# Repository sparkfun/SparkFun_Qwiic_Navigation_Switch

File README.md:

SparkFun Qwiic Navigational Switch
========================================

[](

[*SparkFun Qwiic Navigational Switch (PRT-27576)*](

<Basic description of the part.>

Repository Contents
-------------------

* **.github/workflows** - YAML files used for GitHub Actions and GitHub Pages/mkdocs
* **/Firmware** - Example code
* **/Hardware** - KiCad design files (.kicad_pcb, .kicad_sch, .kicad_pro)
* **/docs** - Online documentation files
  * **/assets** - Folder containing all the file assets used for product documentation
    * **/3d_model** - Exported 3D models from KiCad
    * **/board_files** - Copy of design files used for product documentation
    * **/component_documentation** - Datasheets and manuals for hardware components
    * **/img** - Images for product documentation
  * **/github** - Files stating how to contribute and filing issues used for product documentation
  * **/javascript** - Folder containing custom javascript used for product documentation
  * **/stylesheet** - Folder containing CSS files used for product documentation
* **/overrides** - Customization files used for product documentation
  * **/.icons** - Icons used for GitHub used for product documentation
  * **./partials** - Used for product documentation

Documentation
--------------
* **[Library](https://github.com/sparkfun/SparkFun_I2C_Expander_Arduino_Library)** - Arduino library for the Qwiic Navigational Switch.
* **[Hookup Guide](https://docs.sparkfun.com/SparkFun_Qwiic_Navigation_Switch/)** - Basic hookup guide for the Qwiic Navigational Switch.

Product Versions
----------------
* [PRT-27576](https://www.sparkfun.com/products/27576) - v1.1

Version History
---------------
* v1.1 - Initial Release

License Information
-------------------

This product is _**open source**_!

Please review the LICENSE.md file for license information.

If you have any questions or concerns on licensing, please contact technical support on our [SparkFun forums](https://forum.sparkfun.com/viewforum.php?f=152).

Distributed as-is; no warranty is given.

- Your friends at SparkFun.

_<COLLABORATION CREDIT>_

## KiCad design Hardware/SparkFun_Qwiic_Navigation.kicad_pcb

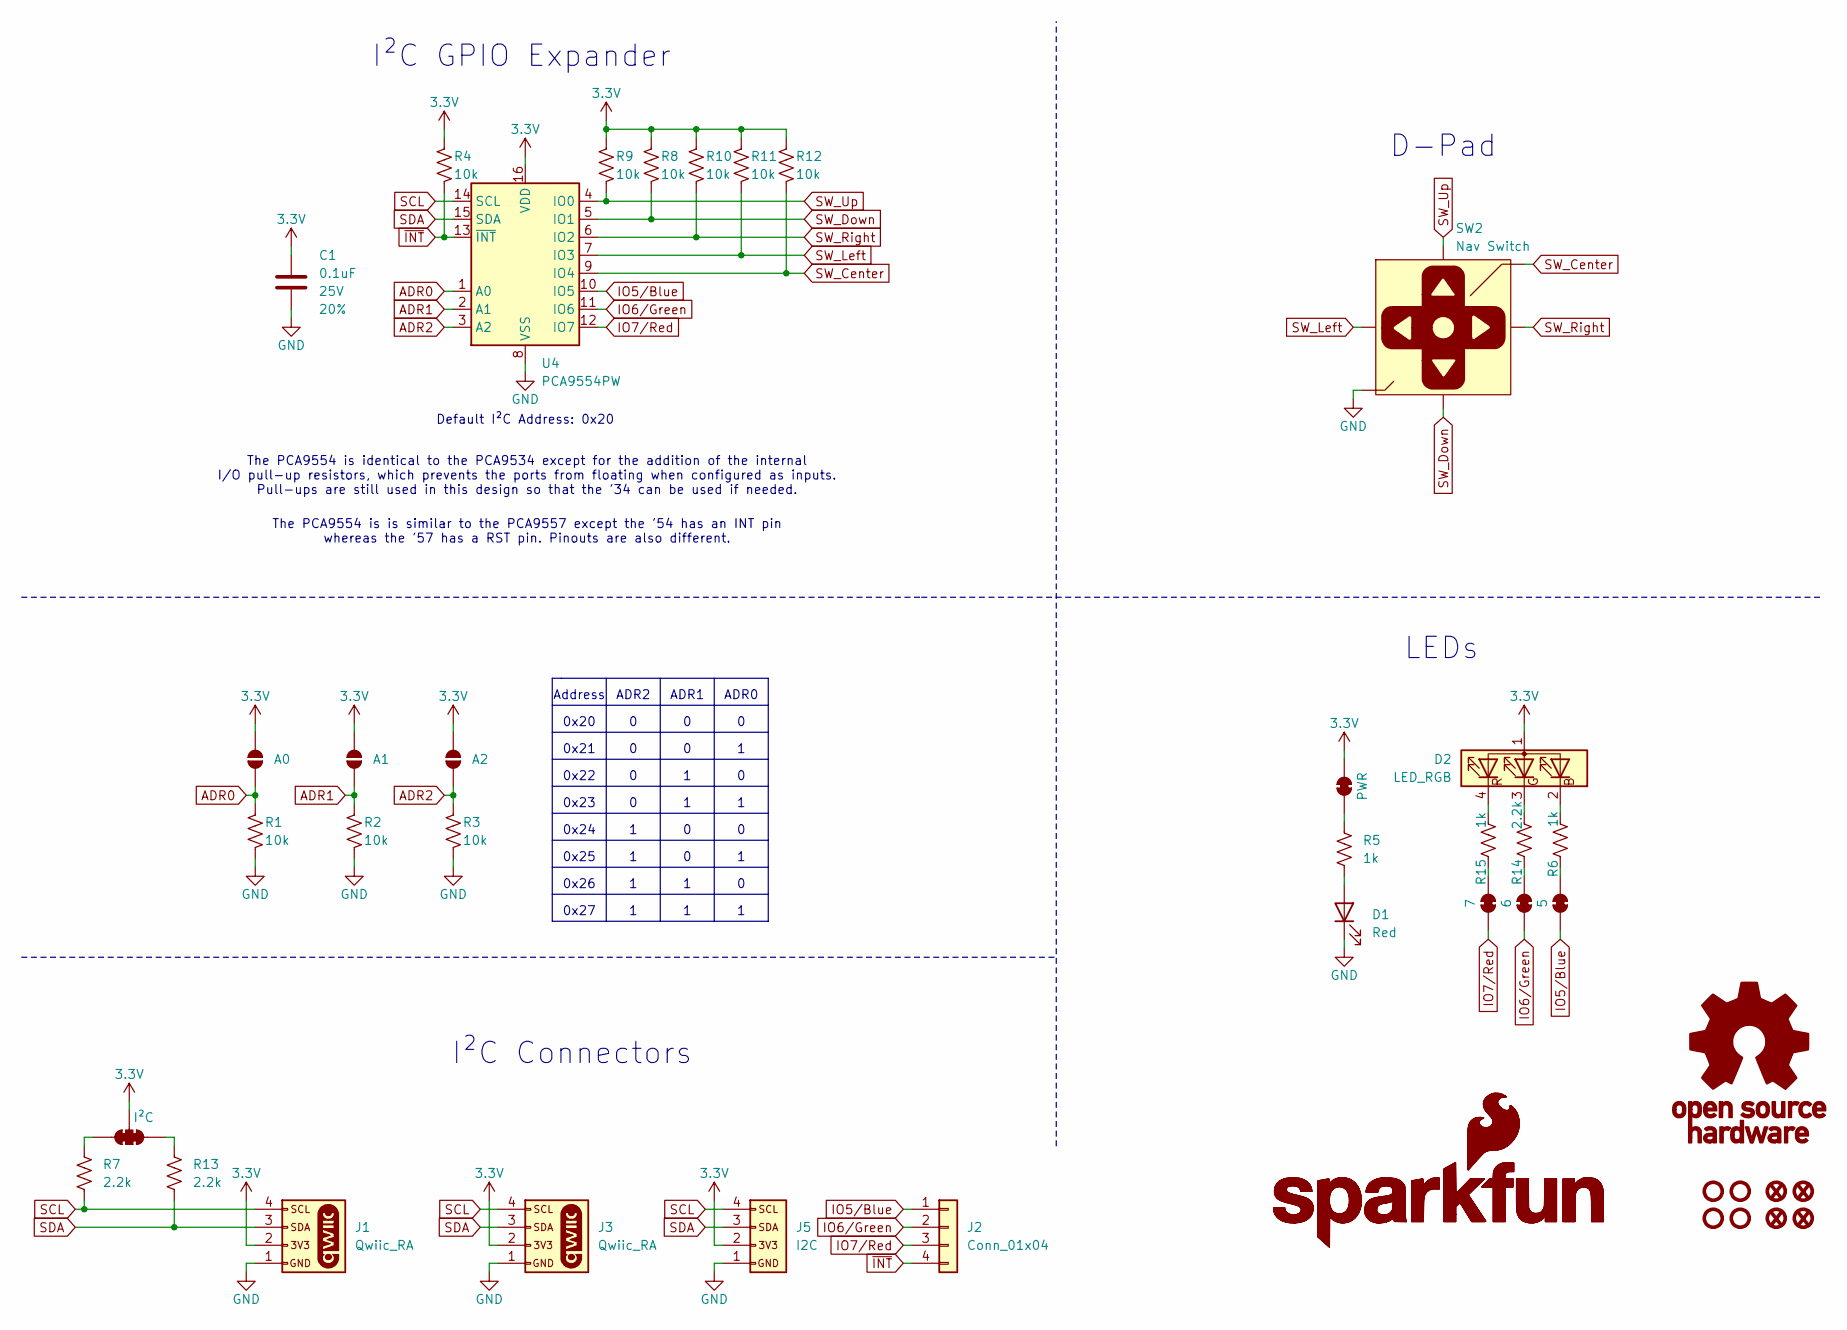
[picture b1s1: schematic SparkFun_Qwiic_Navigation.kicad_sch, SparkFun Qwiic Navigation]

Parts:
C1: 0.1uF; C_0603_1608Metric; Voltage 25V; Tolerance 20%
D1: Red; LED_0603_1608Metric_Red
D2: LED_RGB; LED_1205_RGB_Bottom
FID1, FID2, FID3, FID4: Fiducial_0.5mm; Fiducial_0.5mm_Mask1mm
G1: OSHW_Logo; Creative_Commons_License
G3: SparkFun_Logo
G5: SparkFun_Logo; SparkFun_Logo_8mm
J1, J3: Qwiic_RA; JST_SMD_1.0mm-4_RA
J2: Conn_01x04; 1x04
J5: I2C; 1x04
JP1: A0; Jumper_2_NO
JP2: A1; Jumper_2_NO
JP3: A2; Jumper_2_NO
JP4: PWR; Jumper_2_NC_Trace
JP5: 5; Jumper_2_NC_Trace
JP6: I²C; Jumper_3_NC-2_Trace
JP7: 6; Jumper_2_NC_Trace
JP8: 7; Jumper_2_NC_Trace
R1, R2, R3, R4, R8, R9, R10, R11, R12: 10k; R_0603_1608Metric
R5, R6, R15: 1k; R_0603_1608Metric
R7, R13, R14: 2.2k; R_0603_1608Metric
ST1, ST2, ST3, ST4: Standoff
SW2: Nav Switch; Navigation_SMD_7.5x7.5mm
U4: PCA9554PW; TSSOP-16_4.4x5mm_P0.65mm

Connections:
3.3V: C1.1, D2.1 (A), J1.2, J3.2, J5.2, JP1.2 (B), JP2.2 (B), JP3.2 (B), JP4.2 (B), JP6.2 (C), R4.2, R8.2, R9.2, R10.2, R11.2, R12.2, U4.16 (VDD)
ADR0: JP1.1 (A), R1.2, U4.1 (A0)
ADR1: JP2.1 (A), R2.2, U4.2 (A1)
ADR2: JP3.1 (A), R3.2, U4.3 (A2)
GND: C1.2, D1.1 (K), J1.1, J3.1, J5.1, R1.1, R2.1, R3.1, SW2.2 (GND), U4.8 (VSS)
IO5/Blue: J2.1, JP5.2 (B), U4.10 (IO5)
IO6/Green: J2.2, JP7.2 (B), U4.11 (IO6)
IO7/Red: J2.3, JP8.2 (B), U4.12 (IO7)
unnamed: D1.2 (A), R5.2
unnamed: D2.2 (BK), R6.2
unnamed: D2.3 (GK), R14.2
unnamed: D2.4 (RK), R15.2
unnamed: JP4.1 (A), R5.1
unnamed: JP5.1 (A), R6.1
unnamed: JP6.1 (A), R13.1
unnamed: JP6.3 (B), R7.1
unnamed: JP7.1 (A), R14.1
unnamed: JP8.1 (A), R15.1
SCL: J1.4, J3.4, J5.4, R7.2, U4.14 (SCL)
SDA: J1.3, J3.3, J5.3, R13.2, U4.15 (SDA)
SW_Center: R12.1, SW2.5 (Center), U4.9 (IO4)
SW_Down: R8.1, SW2.3 (Down), U4.5 (IO1)
SW_Left: R11.1, SW2.1 (Left), U4.7 (IO3)
SW_Right: R10.1, SW2.4 (Right), U4.6 (IO2)
SW_Up: R9.1, SW2.6 (Up), U4.4 (IO0)
~INT: J2.4, R4.1, U4.13 (~INT)

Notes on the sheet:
The PCA9554 is is similar to the PCA9557 except the '54 has an INT pin whereas the '57 has a RST pin. Pinouts are also different.
Default I²C Address: 0x20
I²C GPIO Expander
0x20
I²C Connectors
ADR2
ADR0
0x23
The PCA9554 is identical to the PCA9534 except for the addition of the internal I/O pull-up resistors, which prevents the ports from floating when configured as inputs. Pull-ups are still used in this design so that the '34 can be used if needed.
0x22
LEDs
0x25
0x26
0x24
D-Pad
0x27
ADR1
0x21
Address

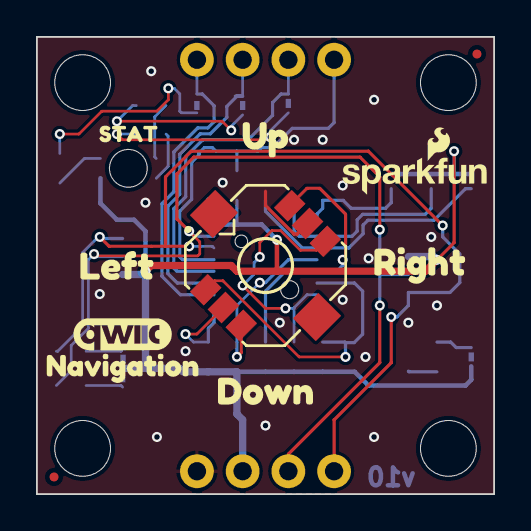
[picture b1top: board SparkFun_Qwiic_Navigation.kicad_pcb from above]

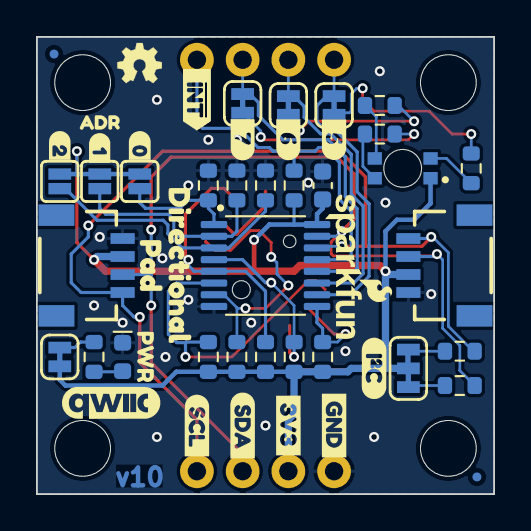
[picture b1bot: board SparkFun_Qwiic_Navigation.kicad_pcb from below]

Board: 2 copper layers, 25.4 x 25.4 mm, 64 parts (48 on the bottom side), 26 nets.

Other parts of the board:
Ref**: Val**; OSHW_Logo_2.5mm
kibuzzard-64C2E6A3: G***; kibuzzard-64C2E6A3
kibuzzard-66EED5D2: G***; kibuzzard-66EED5D2
kibuzzard-66EF6B89: G***; kibuzzard-66EF6B89
kibuzzard-66EF7A0B: G***; kibuzzard-66EF7A0B
kibuzzard-66EF7A03: G***; kibuzzard-66EF7A03
kibuzzard-66EF7A24: G***; kibuzzard-66EF7A24
kibuzzard-66EF7AE6: G***; kibuzzard-66EF7AE6
kibuzzard-66EF7AEF: G***; kibuzzard-66EF7AEF
kibuzzard-66EF7B1E: G***; kibuzzard-66EF7B1E
kibuzzard-66EF7B7C: G***; kibuzzard-66EF7B7C
kibuzzard-66EF7B15: G***; kibuzzard-66EF7B15
kibuzzard-66EF7B78: G***; kibuzzard-66EF7B78
kibuzzard-66EF55AC: G***; kibuzzard-66EF55AC
kibuzzard-66EF79E9: G***; kibuzzard-66EF79E9
kibuzzard-66EF559E: G***; kibuzzard-66EF559E
kibuzzard-66EF5597: G***; kibuzzard-66EF5597
kibuzzard-66F18F5E: G***; kibuzzard-66F18F5E
kibuzzard-66F18F8F: G***; kibuzzard-66F18F8F
kibuzzard-66F18F9B: G***; kibuzzard-66F18F9B
kibuzzard-66F182A6: G***; kibuzzard-66F182A6
kibuzzard-67117BDD: G***; kibuzzard-67117BDD
kibuzzard-6730262A: G***; kibuzzard-6730262A

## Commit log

2024-11-25 Add DRC exclusions
2024-12-03 Update code for PCA9554 Populated on Board
2024-12-03 Initial Push GitHub Pages
2024-12-03 Remove Artifacts from Cloning Directional Pad Repo
2024-12-03 Move/Add Datasheets into Assets Folder
2024-12-03 Export Schematic, Board Files, 3D Model, Board Dimensions
2024-12-04 Update for Navigation Switch
2024-12-05 Screenshot Arduino Output
2025-01-17 Add Product Photos, Highlights, and Hardware Hookup
2025-01-17 Update SCH to v11
2025-01-17 Update copy of KiCad Files for v11
2025-01-17 Update resources links for v11
2025-01-21 Update 3D Model for v11, Fix Typos
2025-01-30 Update product link due to issue with redirecting
2025-01-30 Deployed fdc556d with MkDocs version: 1.6.1
2026-06-03 Deployed b64c0da with MkDocs version: 1.6.1

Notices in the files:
parts and their libraries:
https://creativecommons.org/licenses/by-sa/4.0
Released under the Creative Commons Attribution Share-Alike 4.0 License
